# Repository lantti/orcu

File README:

Odyssee Remote Control Unit

Install bootloader: "avrdude -c arduino -p t44 -b 19200 -P /dev/ttyUSB0 -U flash:w:bootloader.hex -U efuse:w:0xfe:m -U eeprom:w:<channel>,<column>,<row>:m"
Notice that the address is given in the opposite order than usual

Install a module using gui: "python3 orcuadmin.py <channel>"
  Example:
    "python3 orcuadmin.py 2"
    "l ../mods/mod_lrk2.hex"
    "s 0"
    "p"
    "u 0"
    <move cursor over unit to flash>
    "f"
    <if fail repeat "f">

LRK2 gui: "python3 mod_lrk_master.py <channel>"
  Example:
    "python3 mod_lrk_master.py 2"
    "l optimal_palette.csv"
    "s 0"
    "p"
    "pa"
    "i 15 10"
 
GUI usage:
  Cursorkeys move cursor, shift-cursorkeys select and unselect. If nothing is selected then the unit under cursor is selected.
  "s <row>" command selects an entire row, "u <row>" unselects. "p" pings selected units.

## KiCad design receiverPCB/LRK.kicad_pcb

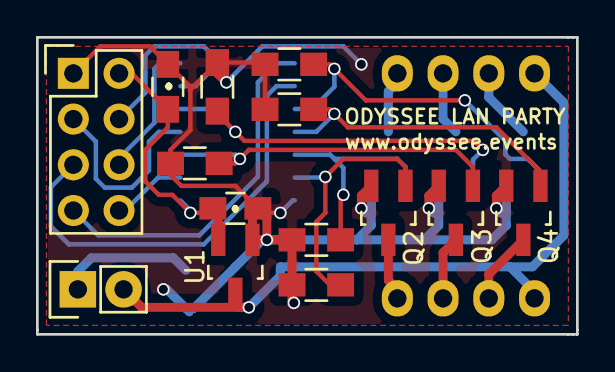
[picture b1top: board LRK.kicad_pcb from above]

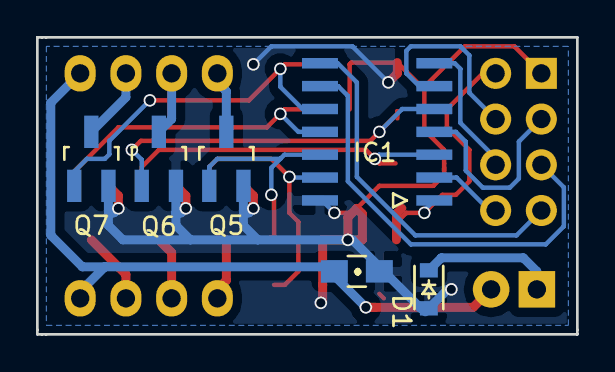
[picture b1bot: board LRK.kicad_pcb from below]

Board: 2 copper layers, 30.0 x 16.5 mm, 22 parts (6 on the bottom side), 22 nets.

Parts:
C2, C3, C4: C; C_0805_HandSoldering
D1: CUS15S30; SOD-323_hand
IC1: ATTINY24A-SS; SOIC-14_hand
P1: PWR; Pin_Header_Straight_1x02
P2: RFMODULE; Pin_Header_Straight_2x04
P3, P4: LEDS; Pin_Header_Straight_1x04
Q2, Q3, Q4, Q5, Q6, Q7: IRLML2402; SOT-23_Handsoldering
R3, R4, R5, R6, R7, R8: R; R_0805_HandSoldering
U1: AP2210; SOT-23_Handsoldering

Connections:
+3V3: C2.1, C4.2, IC1.1, P2.2, U1.2
+12V: C3.1, P1.2, P3.4, P4.4, U1.3
/0V: D1.1, P1.1
/CE|RESET: IC1.4, P2.3
/CSN: IC1.6, P2.4
/IRQ|SCI: IC1.2, P2.8
/MISO|SII: IC1.8, P2.7
/MOSI|SDI: IC1.7, P2.6
/SCK|SDO: IC1.9, P2.5
/ledB1: IC1.11, Q4.1, R5.1
/ledB1_out: P3.3, Q4.3
/ledB2: IC1.10, Q7.1, R8.1
/ledB2_out: P4.3, Q7.3
/ledG1: IC1.3, Q3.1, R4.1
/ledG1_out: P3.2, Q3.3
/ledG2: IC1.5, Q6.1, R7.1
/ledG2_out: P4.2, Q6.3
/ledR1: IC1.13, Q2.1, R3.1
/ledR1_out: P3.1, Q2.3
/ledR2: IC1.12, Q5.1, R6.1
/ledR2_out: P4.1, Q5.3
GND: C2.2, C3.2, C4.1, D1.2, IC1.14, P2.1, Q2.2, Q3.2, Q4.2, Q5.2, Q6.2, Q7.2, R3.2, R4.2, R5.2, R6.2, R7.2, R8.2, U1.1

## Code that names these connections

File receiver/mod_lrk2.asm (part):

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

//expects r17:r16 pointing to colour list, r19:r18 to target buffer. Mangels r10, r9, r8, r7, r6, r5, r16, r17, r18, r19, r20, r21
PIN_TOGGLE_MASKS:       .DB (1<<LEDG1),(1<<LEDG2),(1<<LEDB1),(1<<LEDB2),(1<<LEDR1),(1<<LEDR2)
gen_pwmlist:            ldi r20,4
                        mov r10,r20
                        clr r5
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
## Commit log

2017-09-18 transfer in receiver PCB design from the old LRK repo
2017-09-18 transfer in the old LRK mcu code as basis for the new bootloader
2017-09-19 add bootup reset for rf module registers
2017-10-01 Enable ACK Payload and implement simple ping functionality
2017-10-05 Separate RF module initialization to a subroutine, Add pipe width spec for disabled pipe and dynamic pipe
2017-10-06 remove test outputs from bootloader
2017-10-07 Fix bootloader failing to use vector table for some module calls, Fix off-by-one in flash page calculation,rename output pins
2017-10-07 Include the first test module
2017-10-31 Add two new test modules and a module to do the work of the old LRK code, cleanup bootloader
2017-11-30 Add rgb and indexed colour input features + fix eeprom write size limitation bug
2017-12-01 Add lrk compatibility mode feature and disable pipe 1-3 debug messages
2018-01-29 Add nrf24l01p driver, orcumaster and partial master code for lrk module
2018-02-06 Add admin UI frame
2018-02-15 Separate ui and admin modules, add flashing functionality to admin, fix bugs
2018-02-18 Add controls for the LRK module + fix bugs that popped up in process
2018-02-21 Add raw mode, change crc to two bytes, use cursor position in ui if nothing selected, fix bugs that appeared
2018-02-22 Add readme, fix bugs
2018-02-22 Add examples to readme
2018-02-23 Make flashing function try harder in case of transmission failures
2018-02-27 Mark units that are likely bricked after a failed flashing operation
